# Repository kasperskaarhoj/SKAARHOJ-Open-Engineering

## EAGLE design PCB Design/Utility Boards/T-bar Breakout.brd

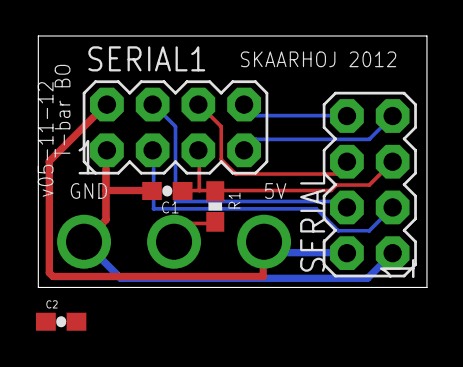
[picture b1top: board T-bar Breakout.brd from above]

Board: 2 copper layers, 21.6 x 14.0 mm, 5 parts (0 on the bottom side), 8 nets.

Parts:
C1: 1uF; 0603-CAP
C2: 10uF; 0603-CAP
R1: 10K; 0603-RES
SERIAL, SERIAL1: M04X2; 2X4

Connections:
5V: C2.1, SERIAL.2, SERIAL1.2
DISP_DATA_OUT: SERIAL.6, SERIAL1.6
GND: C1.2, C2.2, SERIAL.1, SERIAL1.1
I2C_SCL: SERIAL.4, SERIAL1.4
I2C_SDA: SERIAL.3, SERIAL1.3
SDI_MOSI: SERIAL.8, SERIAL1.8
SDI_SCLK: SERIAL.7, SERIAL1.7
SLIDER_IN: C1.1, R1.1, SERIAL.5, SERIAL1.5

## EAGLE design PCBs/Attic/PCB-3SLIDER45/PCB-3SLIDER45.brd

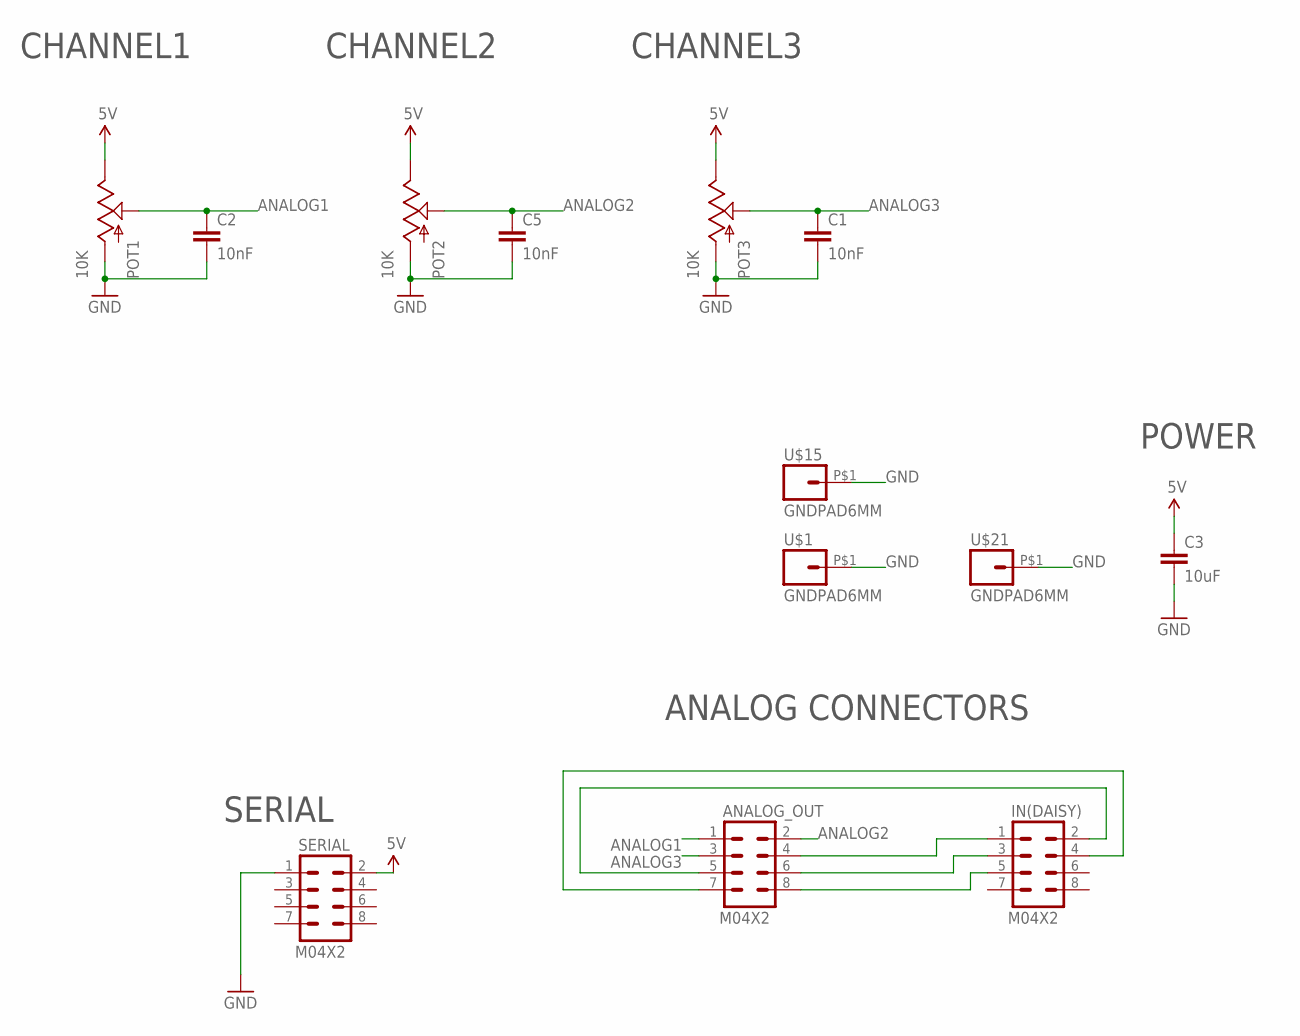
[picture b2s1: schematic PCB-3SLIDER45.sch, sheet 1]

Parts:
ANALOG_OUT: M04X2; 2X4
C1, C2, C5: 10nF; 0603-CAP
C3: 10uF; 0805
IN(DAISY): M04X2; 2X4
POT1, POT2, POT3: 10K; SLIDER45
SERIAL: M04X2; 2X4
U$1, U$15, U$21: GNDPAD6MM; 3.2MMPAD6MM

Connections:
5V: C3.1, POT1.1 (E), POT2.1 (E), POT3.1 (E), SERIAL.2
ANALOG1: ANALOG_OUT.1, C2.1, POT1.2A (S)
ANALOG2: ANALOG_OUT.2, C5.1, POT2.2A (S)
ANALOG3: ANALOG_OUT.3, C1.1, POT3.2A (S)
GND: C1.2, C2.2, C3.2, C5.2, POT1.3 (A), POT2.3 (A), POT3.3 (A), SERIAL.1, U$1.P$1, U$15.P$1, U$21.P$1
unnamed: ANALOG_OUT.4, IN(DAISY).1
unnamed: ANALOG_OUT.5, IN(DAISY).2
unnamed: ANALOG_OUT.6, IN(DAISY).3
unnamed: ANALOG_OUT.7, IN(DAISY).4
unnamed: ANALOG_OUT.8, IN(DAISY).5

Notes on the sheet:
SERIAL
POWER
ANALOG CONNECTORS
CHANNEL3
CHANNEL1
CHANNEL2

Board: 2 copper layers, 13 parts (7 on the bottom side), 10 nets, no tracks yet.

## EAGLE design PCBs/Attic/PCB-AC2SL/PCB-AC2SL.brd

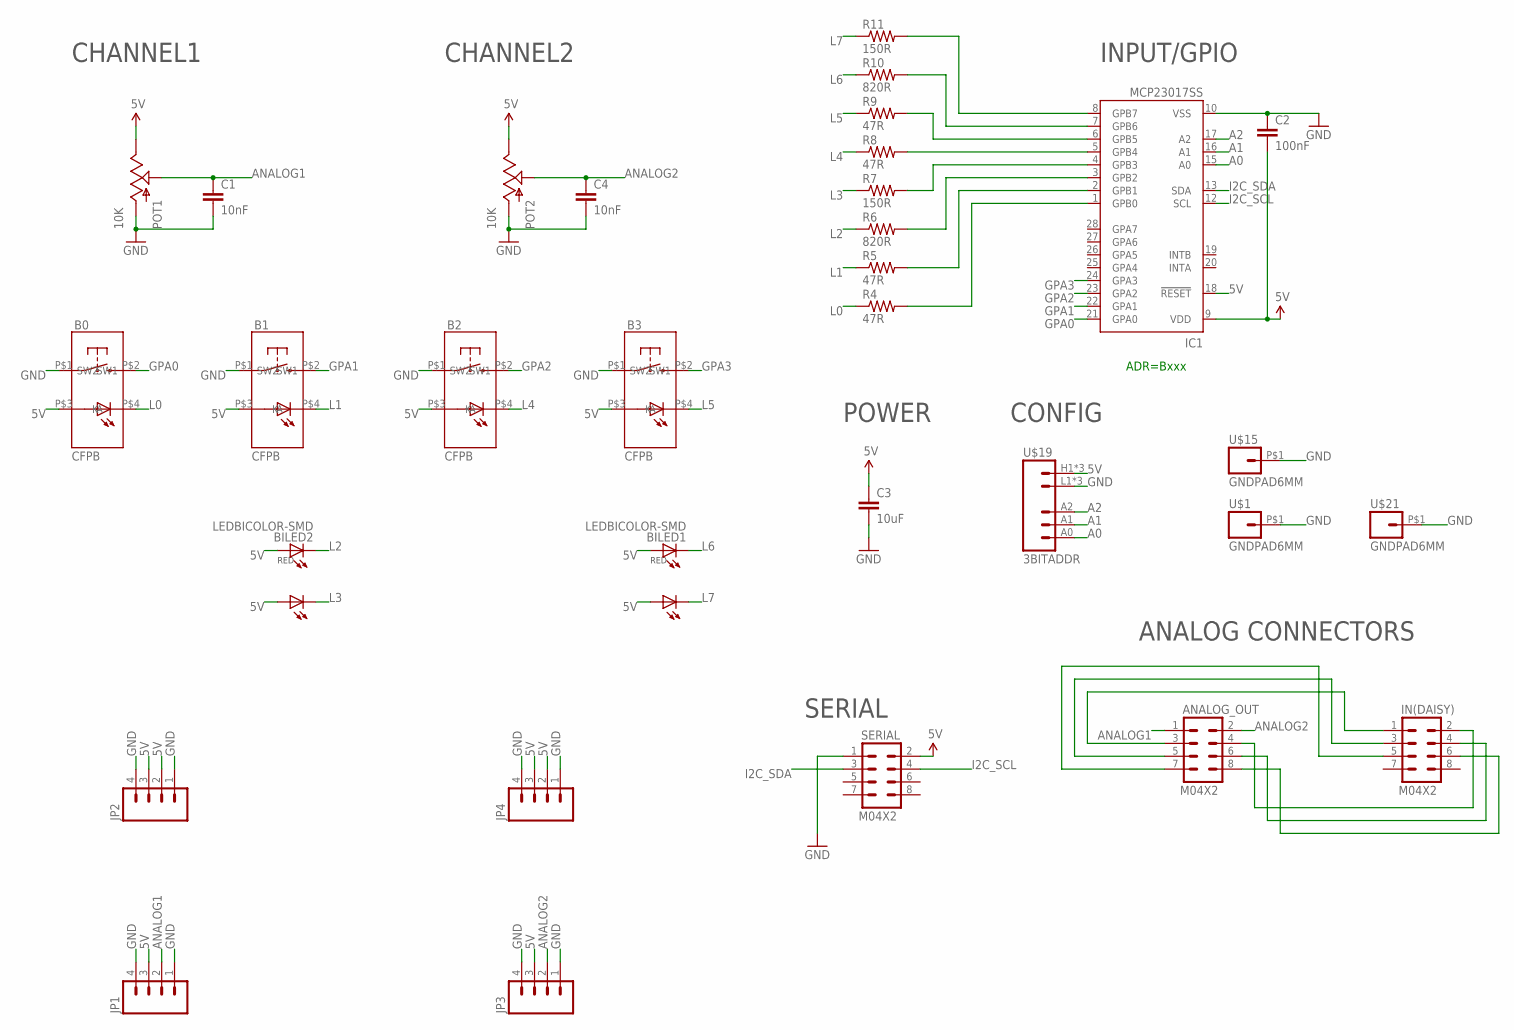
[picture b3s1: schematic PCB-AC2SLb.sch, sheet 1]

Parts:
ANALOG_OUT: M04X2; 2X4
B0, B1, B2, B3: CFPB; CFPB-6/9MM
BILED1, BILED2: LEDBICOLOR-SMD
C1, C4: 10nF; 0603-CAP
C2: 100nF; 0603-CAP
C3: 10uF; 0805
IC1: MCP23017SS; SSOP28; MPN MCP23017-E/SS
IN(DAISY): M04X2; 2X4
JP1, JP2, JP3, JP4: M04PTH; 1X04
POT1, POT2: 10K; SLIDER45
R4, R5, R8, R9: 47R; 0603-RES
R6, R10: 820R; 0603-RES
R7, R11: 150R; 0603-RES
SERIAL: M04X2; 2X4
U$1, U$15, U$21: GNDPAD6MM; 3.2MMPAD6MM
U$19: 3BITADDR

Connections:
5V: B0.P$3 (A), B1.P$3 (A), B2.P$3 (A), B3.P$3 (A), BILED1.P$1 (A), BILED1.P$3 (A1), BILED2.P$1 (A), BILED2.P$3 (A1), C2.2, C3.1, IC1.9 (VDD), IC1.18 (!RESET), JP1.3, JP2.2, JP2.3, JP3.3, JP4.2, JP4.3, POT1.1 (E), POT2.1 (E), SERIAL.2, U$19.H1 (VCC), U$19.H2 (VCC), U$19.H3 (VCC)
A0: IC1.15 (A0), U$19.A0
A1: IC1.16 (A1), U$19.A1
A2: IC1.17 (A2), U$19.A2
ANALOG1: ANALOG_OUT.1, C1.1, JP1.2, POT1.2A (S)
ANALOG2: ANALOG_OUT.2, C4.1, JP3.2, POT2.2A (S)
GND: B0.P$1 (SW1), B1.P$1 (SW1), B2.P$1 (SW1), B3.P$1 (SW1), C1.2, C2.1, C3.2, C4.2, IC1.10 (VSS), JP1.1, JP1.4, JP2.1, JP2.4, JP3.1, JP3.4, JP4.1, JP4.4, POT1.3 (A), POT2.3 (A), SERIAL.1, U$1.P$1, U$15.P$1, U$19.L1 (GND), U$19.L2 (GND), U$19.L3 (GND), U$21.P$1
GPA0: B0.P$2 (SW2), IC1.21 (GPA0)
GPA1: B1.P$2 (SW2), IC1.22 (GPA1)
GPA2: B2.P$2 (SW2), IC1.23 (GPA2)
GPA3: B3.P$2 (SW2), IC1.24 (GPA3)
I2C_SCL: IC1.12 (SCL), SERIAL.4
I2C_SDA: IC1.13 (SDA), SERIAL.3
L0: B0.P$4 (K), R4.1
L1: B1.P$4 (K), R5.1
L2: BILED2.P$2 (C), R6.1
L3: BILED2.P$4 (C1), R7.1
L4: B2.P$4 (K), R8.1
L5: B3.P$4 (K), R9.1
L6: BILED1.P$2 (C), R10.1
L7: BILED1.P$4 (C1), R11.1
unnamed: IC1.4 (GPB3), R7.2
unnamed: IC1.5 (GPB4), R8.2
unnamed: IC1.6 (GPB5), R9.2
unnamed: IC1.7 (GPB6), R10.2
unnamed: IC1.8 (GPB7), R11.2
unnamed: IC1.3 (GPB2), R6.2
unnamed: IC1.2 (GPB1), R5.2
unnamed: IC1.1 (GPB0), R4.2
unnamed: ANALOG_OUT.3, IN(DAISY).1
unnamed: ANALOG_OUT.5, IN(DAISY).3
unnamed: ANALOG_OUT.7, IN(DAISY).5
unnamed: ANALOG_OUT.4, IN(DAISY).2
unnamed: ANALOG_OUT.6, IN(DAISY).4
unnamed: ANALOG_OUT.8, IN(DAISY).6

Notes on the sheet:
SERIAL
ADR=Bxxx
INPUT/GPIO
POWER
ANALOG CONNECTORS
CHANNEL1
CHANNEL2
CONFIG

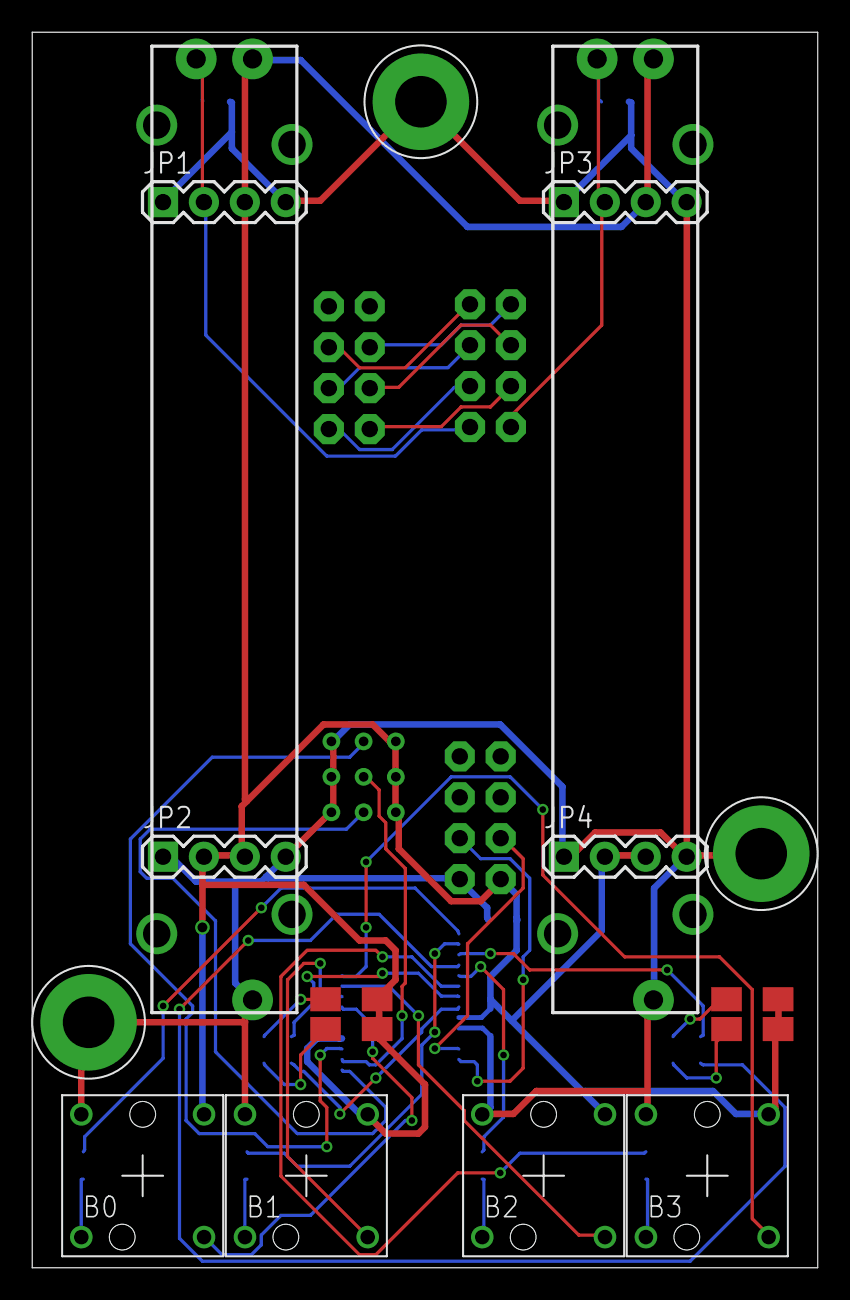
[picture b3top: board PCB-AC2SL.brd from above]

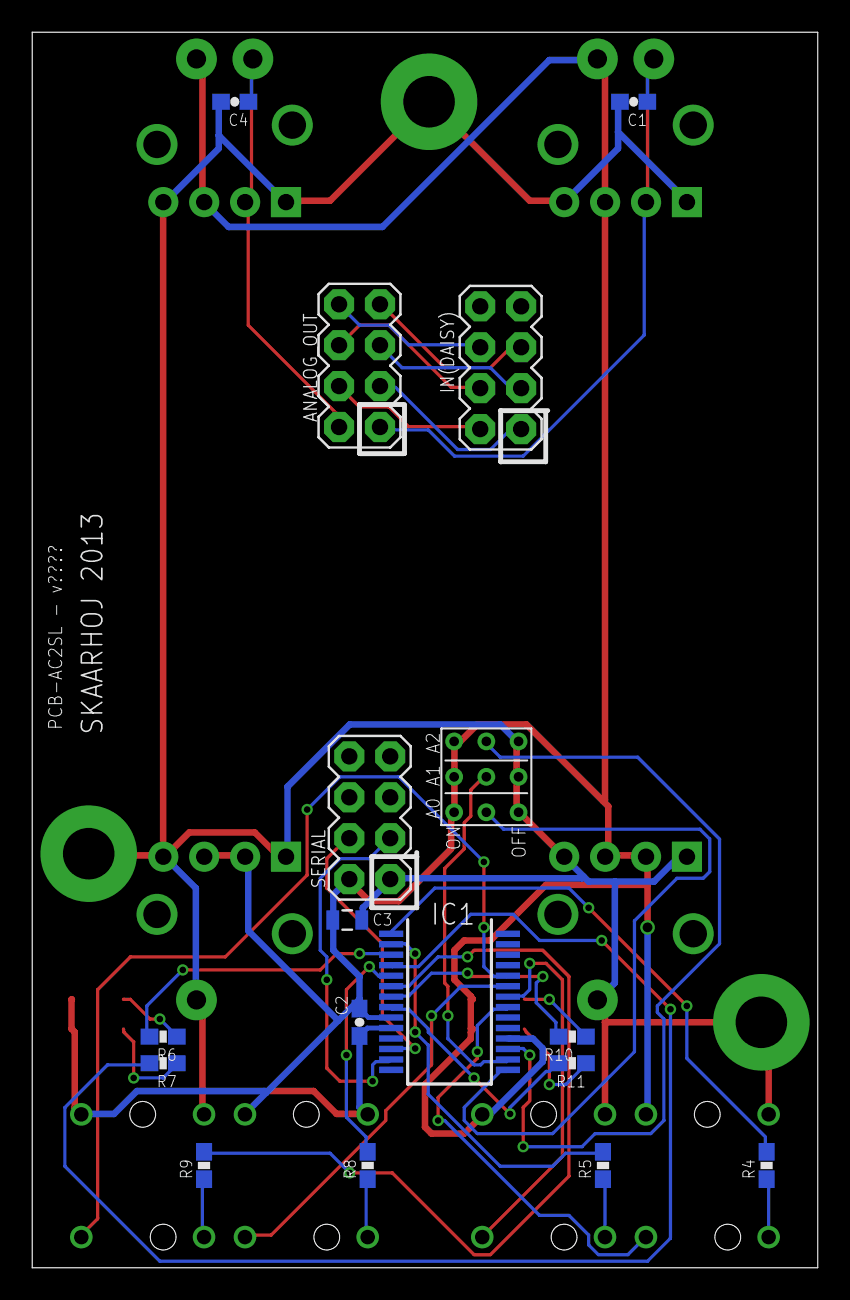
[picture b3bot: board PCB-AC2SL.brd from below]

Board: 2 copper layers, 48.8 x 76.7 mm, 32 parts (17 on the bottom side), 35 nets.

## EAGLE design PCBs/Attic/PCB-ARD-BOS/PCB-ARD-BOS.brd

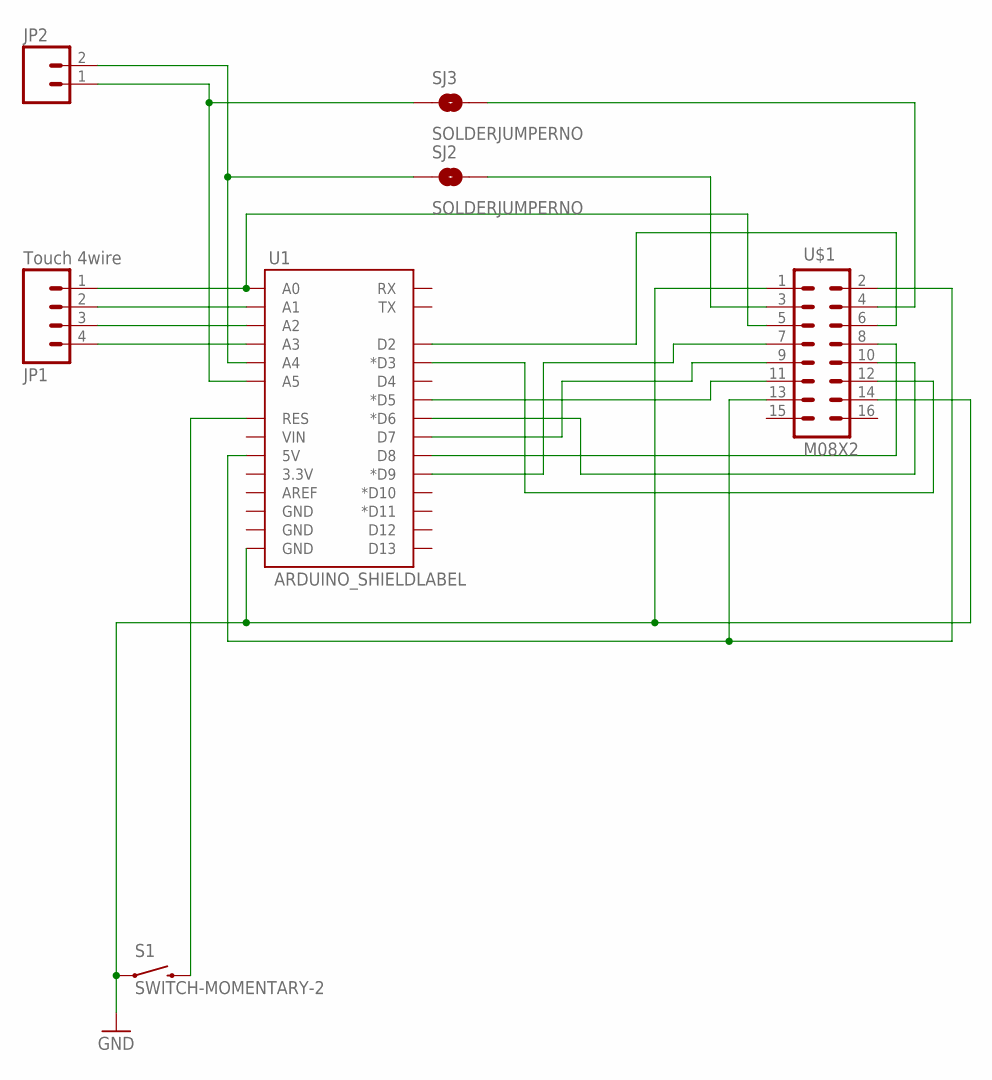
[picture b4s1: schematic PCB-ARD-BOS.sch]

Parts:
JP1: Touch 4wire; 1X04
JP2: M02PTH; 1X02
S1: SWITCH-MOMENTARY-2; TACTILE_SWITCH_TALL
SJ2, SJ3: SOLDERJUMPERNO; SJ_2S-NO
U1: ARDUINO_SHIELDLABEL; DUEMILANOVE_SHIELD
U$1: M08X2; 2X8

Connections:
GND: S1.A2 (1), U1.GND@0 (GND), U$1.1, U$1.14
unnamed: U1.D9 (*D9), U$1.7
unnamed: U1.5V, U$1.2, U$1.13
unnamed: JP2.2, SJ2.1, U1.A4
unnamed: JP2.1, SJ3.1, U1.A5
unnamed: JP1.1, U1.A0, U$1.5
unnamed: U1.D2, U$1.6
unnamed: U1.D5 (*D5), U$1.11
unnamed: U1.D8, U$1.8
unnamed: U1.D7, U$1.9
unnamed: U1.D6 (*D6), U$1.10
unnamed: JP1.2, U1.A1
unnamed: U1.D3 (*D3), U$1.12
unnamed: SJ3.2, U$1.4
unnamed: JP1.3, U1.A2
unnamed: JP1.4, U1.A3
unnamed: SJ2.2, U$1.3
unnamed: S1.B2 (2), U1.RES

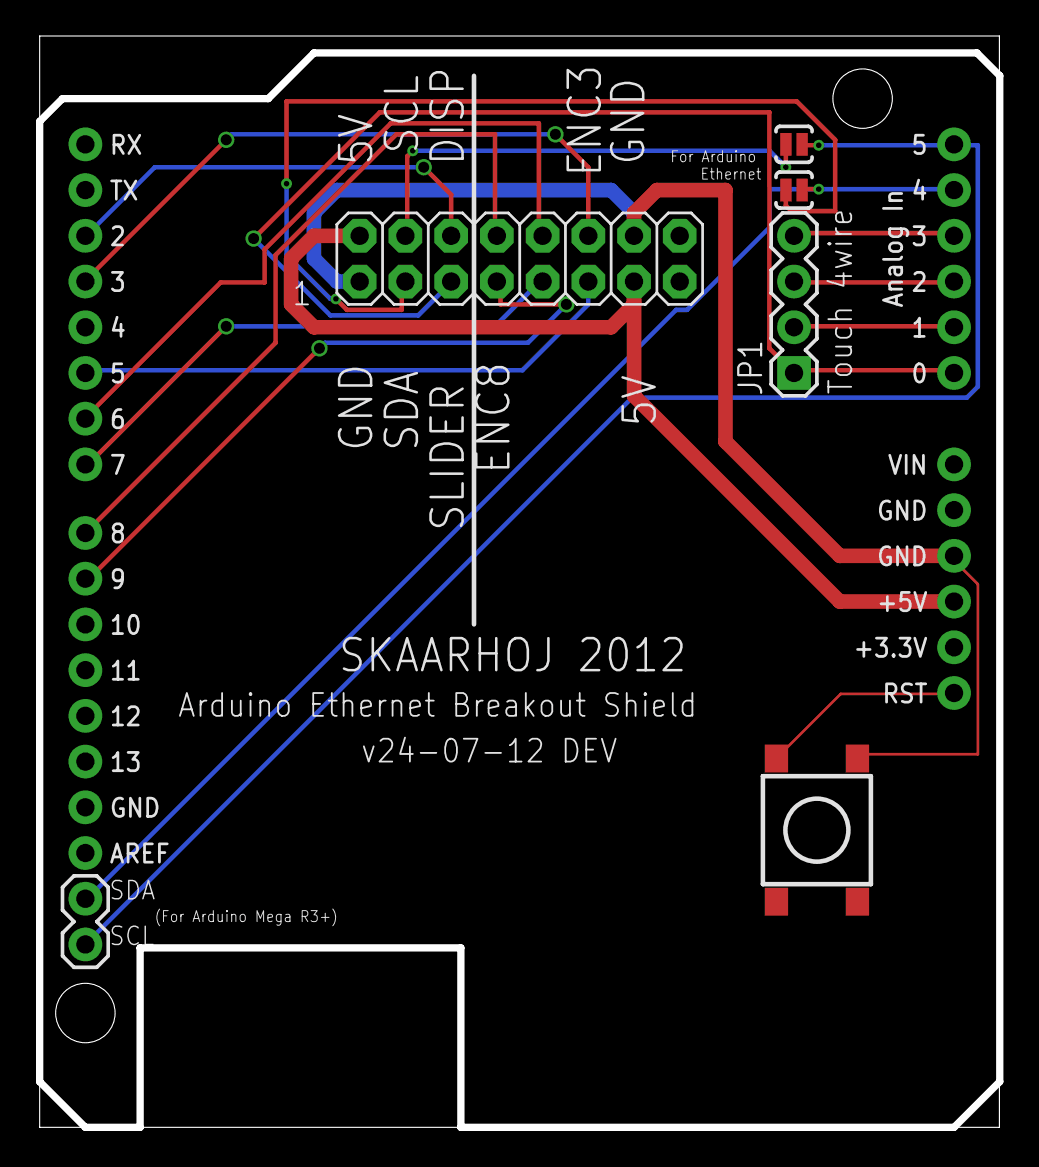
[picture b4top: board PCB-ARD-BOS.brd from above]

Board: 2 copper layers, 53.3 x 60.6 mm, 7 parts (0 on the bottom side), 18 nets.

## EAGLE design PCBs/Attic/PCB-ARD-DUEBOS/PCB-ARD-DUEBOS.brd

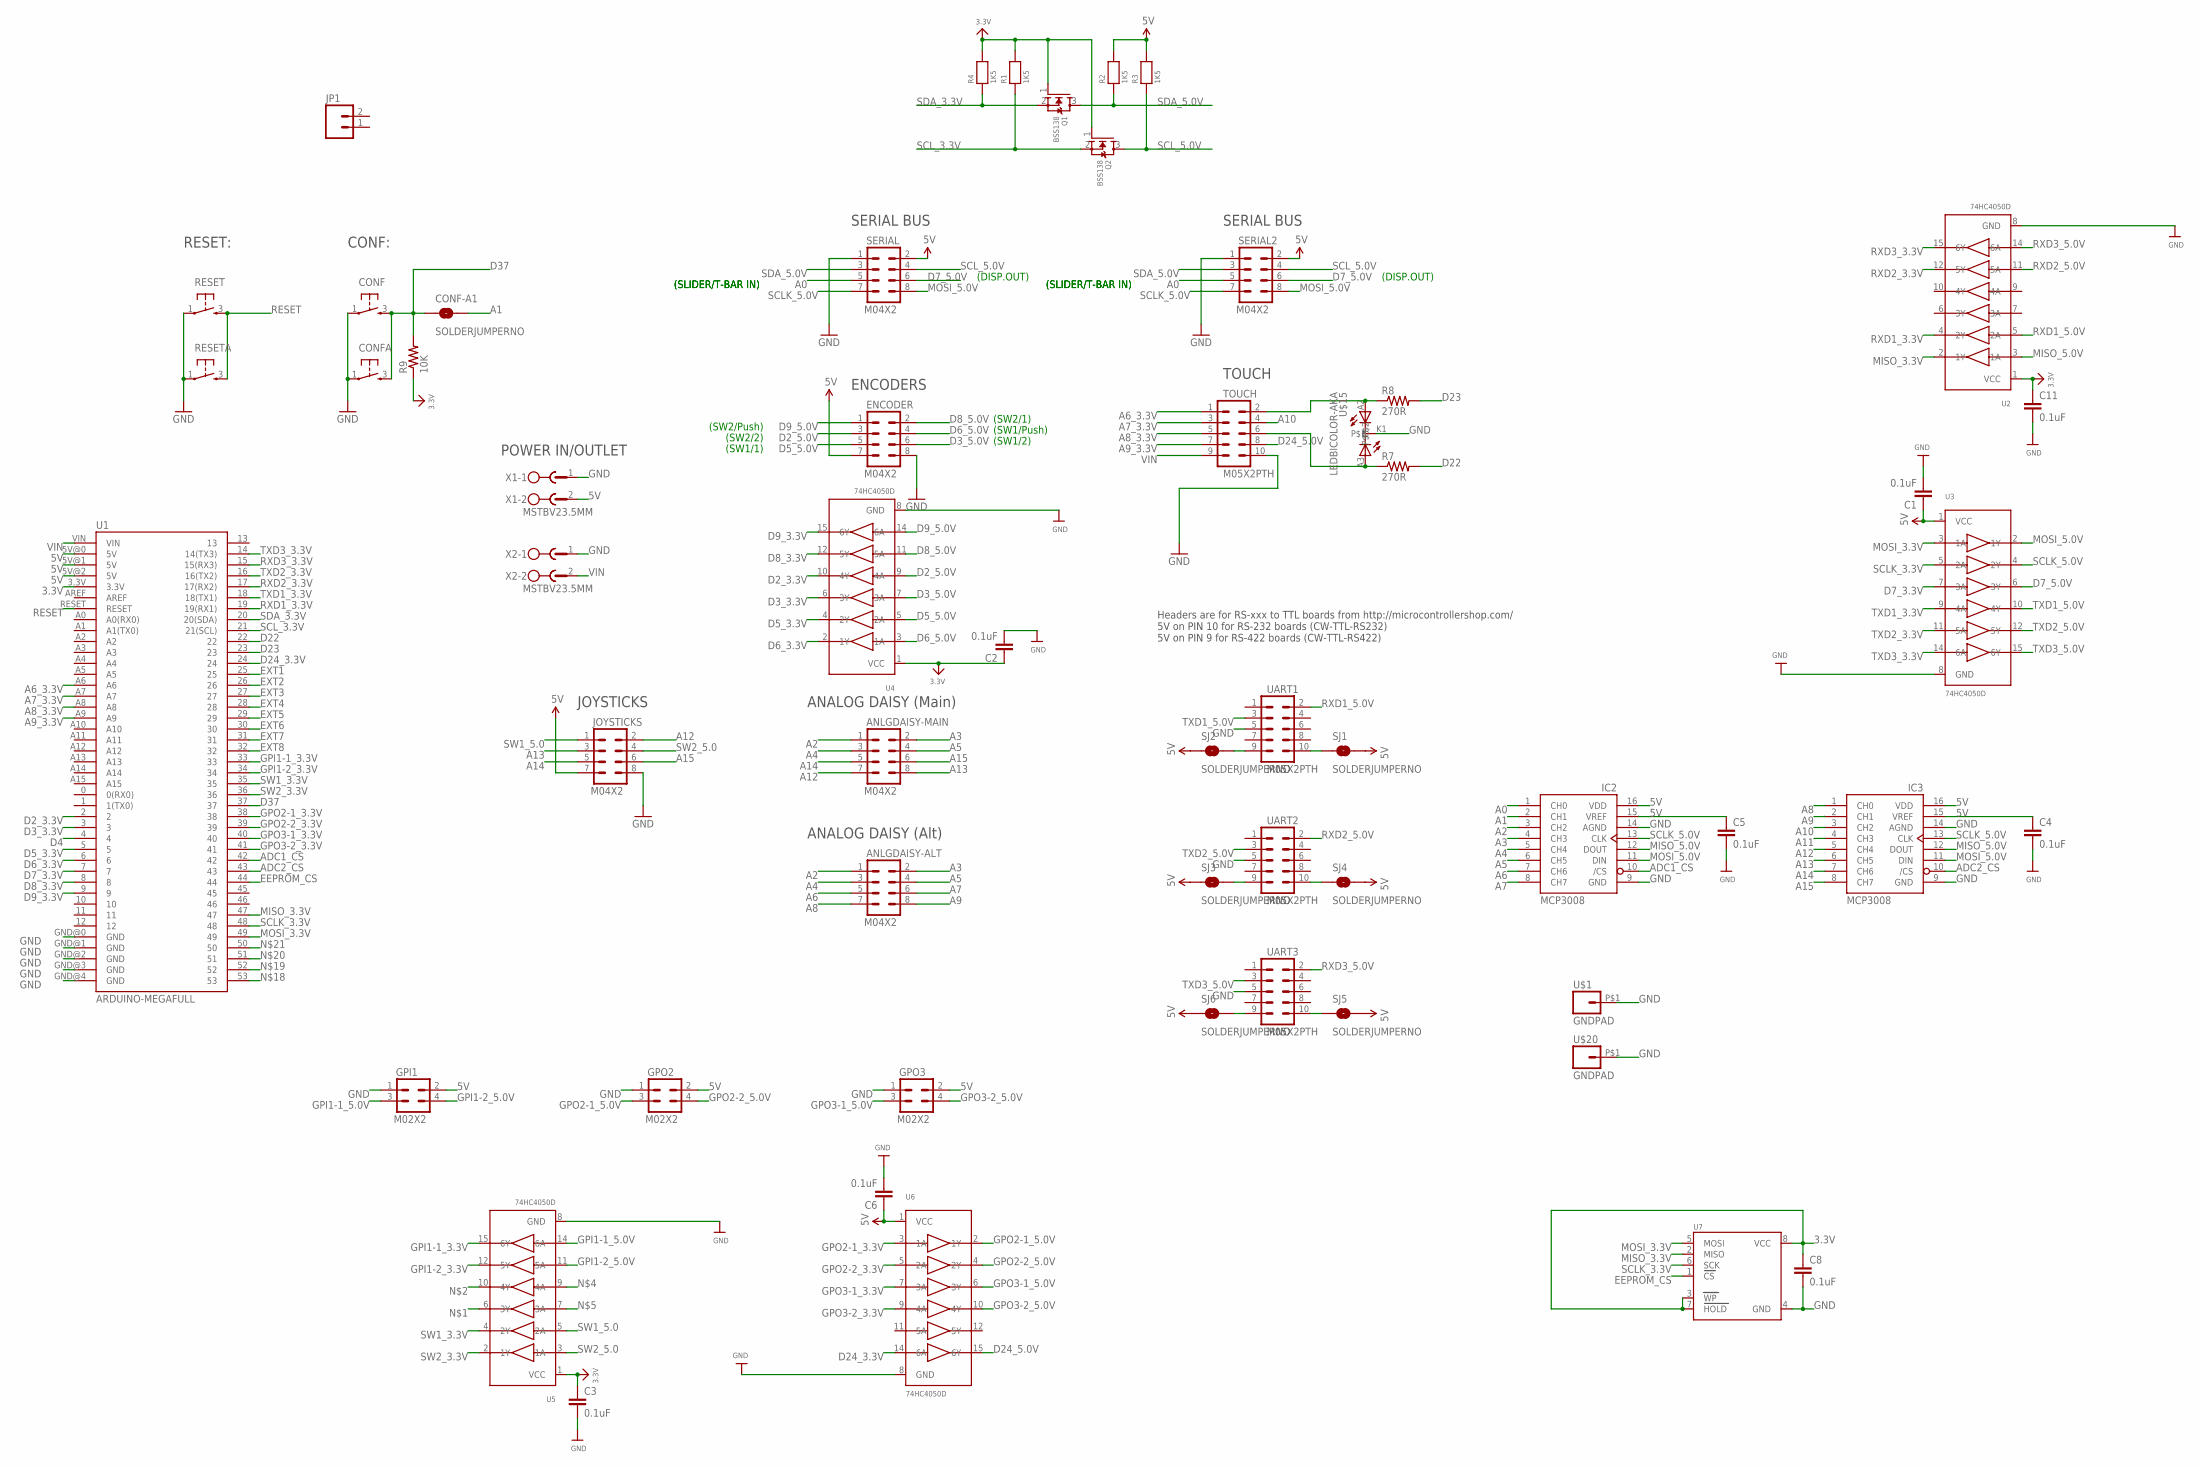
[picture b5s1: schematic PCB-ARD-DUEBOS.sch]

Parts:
ANLGDAISY-ALT: M04X2; 2X4
ANLGDAISY-MAIN: M04X2; 2X4
C1, C2, C3, C4, C5, C6, C8, C11: 0.1uF; 0603-CAP
CONF: TAC_SWITCH; PUSHBUTTON
CONF-A1: SOLDERJUMPERNO; SJ_2S-NO
CONFA: TAC_SWITCH; PUSHBUTTON
ENCODER: M04X2; 2X4
GPI1: M02X2; 2X2
GPO2, GPO3: M02X2; 2X2
IC2, IC3: MCP3008SOIC; SOIC16
JOYSTICKS: M04X2; 2X4
JP1: M02PTH; 1X02
Q1, Q2: BSS138; SOT23-R
R1, R2, R3, R4: 1K5; 0603
R7, R8: 270R; 0603-RES
R9: 10K; 0603-RES
RESET: TAC_SWITCH; PUSHBUTTON
RESETA: TAC_SWITCH; PUSHBUTTON
SERIAL, SERIAL2: M04X2; 2X4
SJ1, SJ2, SJ3, SJ4, SJ5, SJ6: SOLDERJUMPERNO; SJ_2S-NO
TOUCH: M05X2PTH; AVR_ICSP
U1: ARDUINO-MEGAFULL; ARDUINO_MEGA
U2, U3, U4, U5, U6: 74HC4050D; TSSOP16
U7: EEPROM_SPI_AT25040ATSSOP; TSSOP8-4.4MM
U$1, U$20: GNDPAD; 3.2MMPAD
U$15: LEDBICOLOR-AKA; LED5MM-BICOLOR
UART1, UART2, UART3: M05X2PTH; AVR_ICSP
X1, X2: MSTBV23.5MM; MSTBV2-3.5

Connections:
3.3V: C2.1, C3.1, C8.1, C11.1, Q1.1 (G), Q2.1 (G), R1.2, R4.2, R9.1, U1.3.3V, U2.1 (VCC), U4.1 (VCC), U5.1 (VCC), U7.3 (WP), U7.7 (HOLD), U7.8 (VCC)
5V: C1.1, C4.1, C5.1, C6.1, ENCODER.7, GPI1.2, GPO2.2, GPO3.2, IC2.15 (VREF), IC2.16 (VDD), IC3.15 (VREF), IC3.16 (VDD), JOYSTICKS.7, R2.2, R3.2, SERIAL.2, SERIAL2.2, SJ1.2, SJ2.1, SJ3.1, SJ4.2, SJ5.2, SJ6.1, U1.5V@0 (5V), U1.5V@1 (5V), U1.5V@2 (5V), U3.1 (VCC), U6.1 (VCC), X1.2
A0: IC2.1 (CH0), SERIAL.5, SERIAL2.5
A1: CONF-A1.2, IC2.2 (CH1)
A2: ANLGDAISY-ALT.1, ANLGDAISY-MAIN.1, IC2.3 (CH2)
A3: ANLGDAISY-ALT.2, ANLGDAISY-MAIN.2, IC2.4 (CH3)
A4: ANLGDAISY-ALT.3, ANLGDAISY-MAIN.3, IC2.5 (CH4)
A5: ANLGDAISY-ALT.4, ANLGDAISY-MAIN.4, IC2.6 (CH5)
A6: ANLGDAISY-ALT.5, IC2.7 (CH6)
A6_3.3V: TOUCH.1, U1.A6
A7: ANLGDAISY-ALT.6, IC2.8 (CH7)
A7_3.3V: TOUCH.3, U1.A7
A8: ANLGDAISY-ALT.7, IC3.1 (CH0)
A8_3.3V: TOUCH.5, U1.A8
A9: ANLGDAISY-ALT.8, IC3.2 (CH1)
A9_3.3V: TOUCH.7, U1.A9
A10: IC3.3 (CH2), TOUCH.4
A11: IC3.4 (CH3)
A12: ANLGDAISY-MAIN.7, IC3.5 (CH4), JOYSTICKS.2
A13: ANLGDAISY-MAIN.8, IC3.6 (CH5), JOYSTICKS.3
A14: ANLGDAISY-MAIN.5, IC3.7 (CH6), JOYSTICKS.5
A15: ANLGDAISY-MAIN.6, IC3.8 (CH7), JOYSTICKS.6
ADC1_CS: IC2.10 (/CS), U1.42
ADC2_CS: IC3.10 (/CS), U1.43
D2_3.3V: U1.2, U4.10 (4Y)
D2_5.0V: ENCODER.3, U4.9 (4A)
D3_3.3V: U1.3, U4.6 (3Y)
D3_5.0V: ENCODER.6, U4.7 (3A)
D4: U1.4
D5_3.3V: U1.5, U4.4 (2Y)
D5_5.0V: ENCODER.5, U4.5 (2A)
D6_3.3V: U1.6, U4.2 (1Y)
D6_5.0V: ENCODER.4, U4.3 (1A)
D7_3.3V: U1.7, U3.7 (3A)
D7_5.0V: SERIAL.6, SERIAL2.6, U3.6 (3Y)
D8_3.3V: U1.8, U4.12 (5Y)
D8_5.0V: ENCODER.2, U4.11 (5A)
D9_3.3V: U1.9, U4.15 (6Y)
D9_5.0V: ENCODER.1, U4.14 (6A)
D22: R7.2, U1.22
D23: R8.2, U1.23
D24_3.3V: U1.24, U6.14 (6A)
D24_5.0V: TOUCH.8, U6.15 (6Y)
D37: CONF.3, CONF-A1.1, CONFA.3, R9.2, U1.37
EEPROM_CS: U1.44, U7.1 (CS)
EXT1: U1.25
EXT2: U1.26
EXT3: U1.27
EXT4: U1.28
EXT5: U1.29
EXT6: U1.30
EXT7: U1.31
EXT8: U1.32
GND: C1.2, C2.2, C3.2, C4.2, C5.2, C6.2, C8.2, C11.2, CONF.1, CONFA.1, ENCODER.8, GPI1.1, GPO2.1, GPO3.1, IC2.9 (GND), IC2.14 (AGND), IC3.9 (GND), IC3.14 (AGND), JOYSTICKS.8, RESET.1, RESETA.1, SERIAL.1, SERIAL2.1, TOUCH.10, U1.GND@0 (GND), U1.GND@1 (GND), U1.GND@2 (GND), U1.GND@3 (GND), U1.GND@4 (GND), U2.8 (GND), U3.8 (GND), U4.8 (GND), U5.8 (GND), U6.8 (GND), U7.4 (GND), U$1.P$1, U$15.K1, U$20.P$1, UART1.5, UART2.5, UART3.5, X1.1, X2.1
GPI1-1_3.3V: U1.33, U5.15 (6Y)
GPI1-1_5.0V: GPI1.3, U5.14 (6A)
GPI1-2_3.3V: U1.34, U5.12 (5Y)
GPI1-2_5.0V: GPI1.4, U5.11 (5A)
GPO2-1_3.3V: U1.38, U6.3 (1A)
GPO2-1_5.0V: GPO2.3, U6.2 (1Y)
GPO2-2_3.3V: U1.39, U6.5 (2A)
GPO2-2_5.0V: GPO2.4, U6.4 (2Y)
GPO3-1_3.3V: U1.40, U6.7 (3A)
GPO3-1_5.0V: GPO3.3, U6.6 (3Y)
GPO3-2_3.3V: U1.41, U6.9 (4A)
GPO3-2_5.0V: GPO3.4, U6.10 (4Y)
MISO_3.3V: U1.47, U2.2 (1Y), U7.2 (MISO)
MISO_5.0V: IC2.12 (DOUT), IC3.12 (DOUT), U2.3 (1A)
MOSI_3.3V: U1.49, U3.3 (1A), U7.5 (MOSI)
MOSI_5.0V: IC2.11 (DIN), IC3.11 (DIN), SERIAL.8, SERIAL2.8, U3.2 (1Y)
unnamed: SJ6.2, UART3.9
unnamed: SJ3.2, UART2.9
unnamed: SJ2.2, UART1.9
unnamed: SJ1.1, UART1.10
unnamed: SJ4.1, UART2.10
unnamed: SJ5.1, UART3.10
unnamed: R8.1, TOUCH.2, U$15.A2
unnamed: R7.1, TOUCH.6, U$15.A3
RESET: RESET.3, RESETA.3, U1.RESET
RXD1_3.3V: U1.19 (19(RX1)), U2.4 (2Y)
RXD1_5.0V: U2.5 (2A), UART1.2
RXD2_3.3V: U1.17 (17(RX2)), U2.12 (5Y)
RXD2_5.0V: U2.11 (5A), UART2.2
RXD3_3.3V: U1.15 (15(RX3)), U2.15 (6Y)
RXD3_5.0V: U2.14 (6A), UART3.2
SCLK_3.3V: U1.48, U3.5 (2A), U7.6 (SCK)
SCLK_5.0V: IC2.13 (CLK), IC3.13 (CLK), SERIAL.7, SERIAL2.7, U3.4 (2Y)
SCL_3.3V: Q2.2 (S), R1.1, U1.21 (21(SCL))
SCL_5.0V: Q2.3 (D), R3.1, SERIAL.4, SERIAL2.4
SDA_3.3V: Q1.2 (S), R4.1, U1.20 (20(SDA))
SDA_5.0V: Q1.3 (D), R2.1, SERIAL.3, SERIAL2.3
SW1_3.3V: U1.35, U5.4 (2Y)
SW1_5.0: JOYSTICKS.1, U5.5 (2A)
SW2_3.3V: U1.36, U5.2 (1Y)
SW2_5.0: JOYSTICKS.4, U5.3 (1A)
TXD1_3.3V: U1.18 (18(TX1)), U3.9 (4A)
TXD1_5.0V: U3.10 (4Y), UART1.3
TXD2_3.3V: U1.16 (16(TX2)), U3.11 (5A)
TXD2_5.0V: U3.12 (5Y), UART2.3
TXD3_3.3V: U1.14 (14(TX3)), U3.14 (6A)
TXD3_5.0V: U3.15 (6Y), UART3.3
VIN: TOUCH.9, U1.VIN, X2.2

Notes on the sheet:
JOYSTICKS
Headers are for RS-xxx to TTL boards from http://microcontrollershop.com/ 5V on PIN 10 for RS-232 boards (CW-TTL-RS232) 5V on PIN 9 for RS-422 boards (CW-TTL-RS422)
ENCODERS
SERIAL BUS
TOUCH
(SLIDER/T-BAR IN)
(SW2/Push)
(SW2/2)
(SW1/1)
(SW2/1)
(SW1/Push)
(SW1/2)
(DISP.OUT)
RESET:
CONF:
ANALOG DAISY (Main)
ANALOG DAISY (Alt)
POWER IN/OUTLET

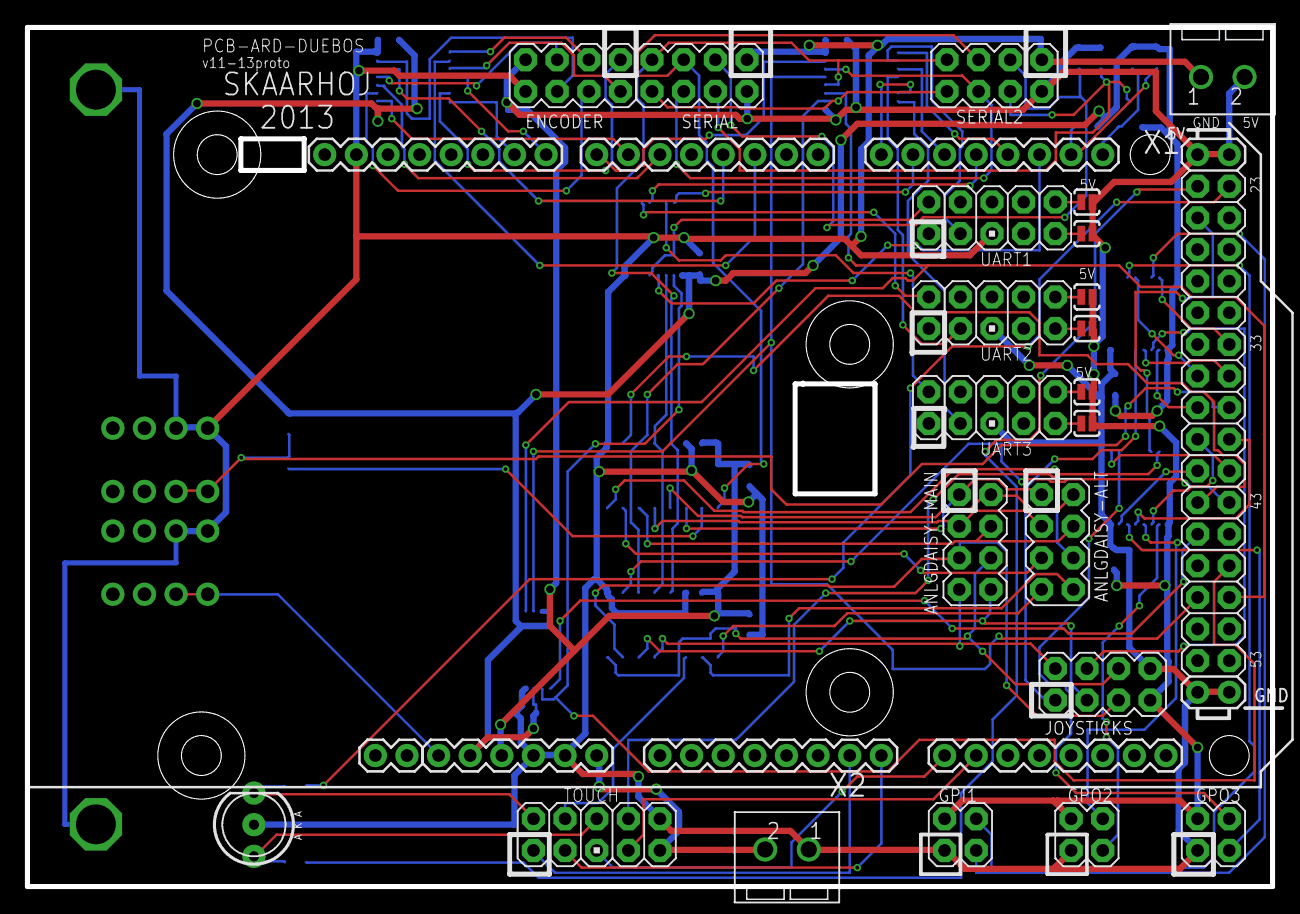
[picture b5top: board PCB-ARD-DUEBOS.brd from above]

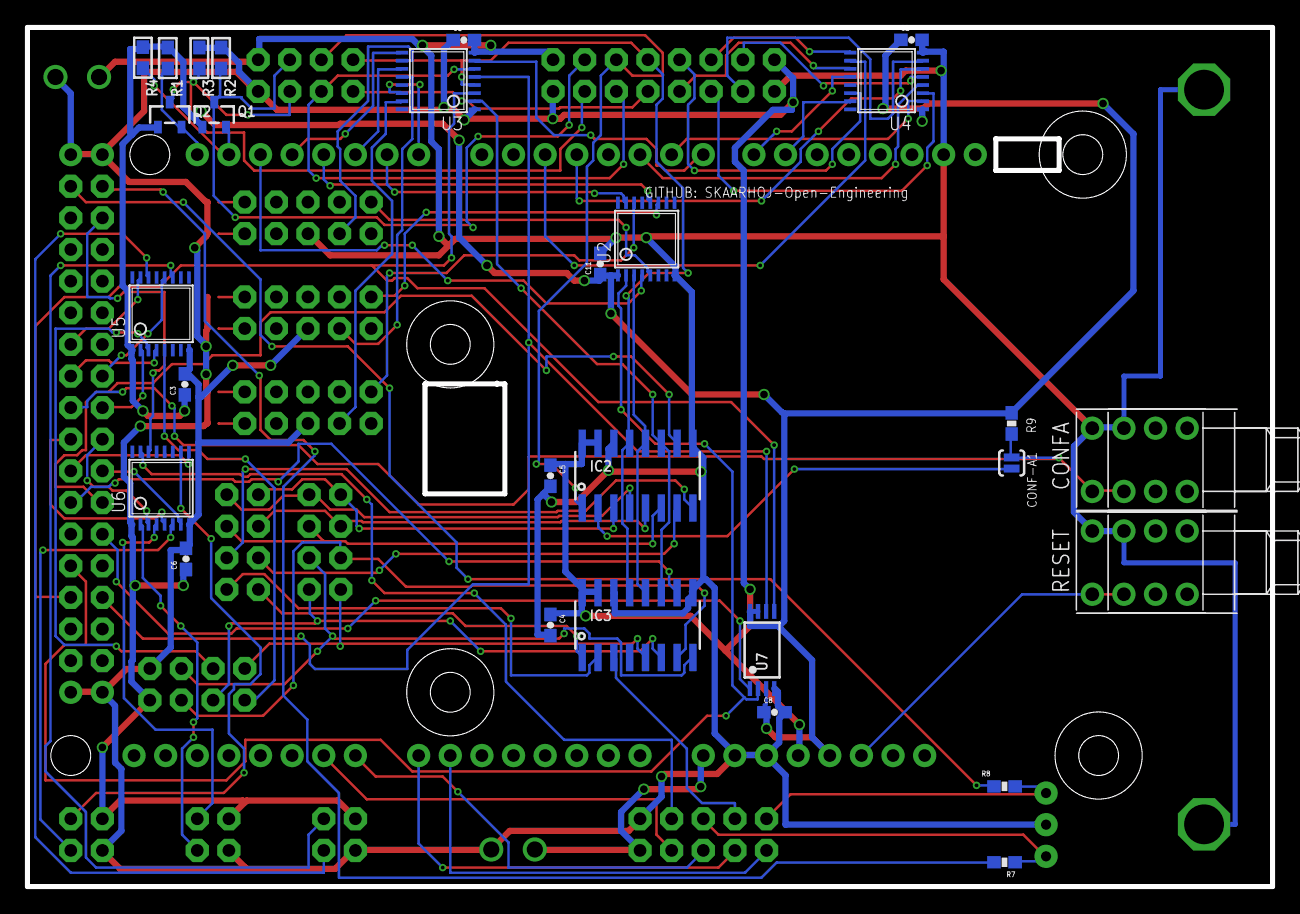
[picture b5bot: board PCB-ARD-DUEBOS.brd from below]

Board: 2 copper layers, 100.0 x 69.0 mm, 56 parts (30 on the bottom side), 92 nets.

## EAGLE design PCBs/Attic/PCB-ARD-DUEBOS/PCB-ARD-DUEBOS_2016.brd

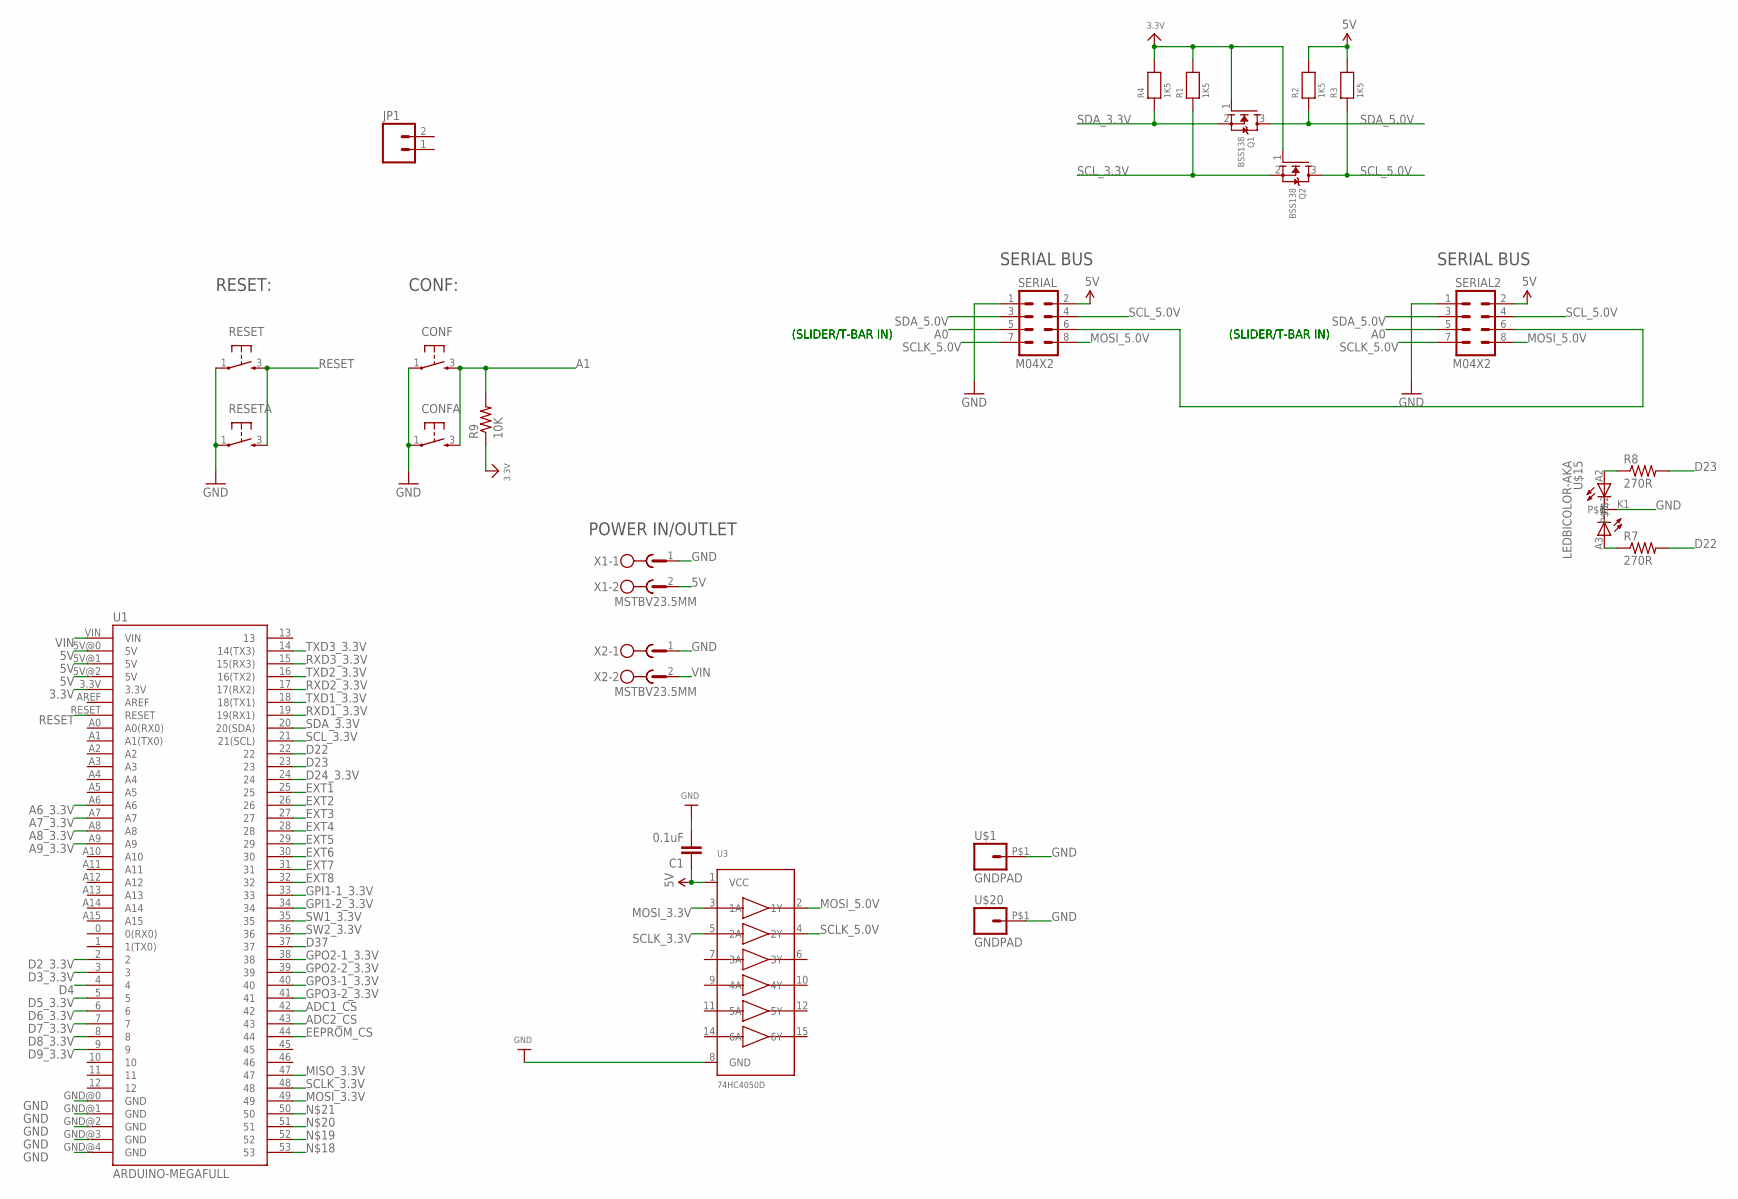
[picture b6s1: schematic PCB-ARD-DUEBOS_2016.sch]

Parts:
C1: 0.1uF; 0603-CAP
CONF: TAC_SWITCH; PUSHBUTTON
CONFA: TAC_SWITCH; PUSHBUTTON
JP1: M02PTH; 1X02
Q1, Q2: BSS138; SOT23-R
R1, R2, R3, R4: 1K5; 0603
R7, R8: 270R; 0603-RES
R9: 10K; 0603-RES
RESET: TAC_SWITCH; PUSHBUTTON
RESETA: TAC_SWITCH; PUSHBUTTON
SERIAL, SERIAL2: M04X2; 2X4
U1: ARDUINO-MEGAFULL; ARDUINO_MEGA
U3: 74HC4050D; TSSOP16
U$1, U$20: GNDPAD; 3.2MMPAD
U$15: LEDBICOLOR-AKA; LED5MM-BICOLOR
X1, X2: MSTBV23.5MM; MSTBV2-3.5

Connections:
3.3V: Q1.1 (G), Q2.1 (G), R1.2, R4.2, R9.1, U1.3.3V
5V: C1.1, R2.2, R3.2, SERIAL.2, SERIAL2.2, U1.5V@0 (5V), U1.5V@1 (5V), U1.5V@2 (5V), U3.1 (VCC), X1.2
A0: SERIAL.5, SERIAL2.5
A1: CONF.3, CONFA.3, R9.2
A6_3.3V: U1.A6
A7_3.3V: U1.A7
A8_3.3V: U1.A8
A9_3.3V: U1.A9
ADC1_CS: U1.42
ADC2_CS: U1.43
D2_3.3V: U1.2
D3_3.3V: U1.3
D4: U1.4
D5_3.3V: U1.5
D6_3.3V: U1.6
D7_3.3V: U1.7
D8_3.3V: U1.8
D9_3.3V: U1.9
D22: R7.2, U1.22
D23: R8.2, U1.23
D24_3.3V: U1.24
D37: U1.37
EEPROM_CS: U1.44
EXT1: U1.25
EXT2: U1.26
EXT3: U1.27
EXT4: U1.28
EXT5: U1.29
EXT6: U1.30
EXT7: U1.31
EXT8: U1.32
GND: C1.2, CONF.1, CONFA.1, RESET.1, RESETA.1, SERIAL.1, SERIAL2.1, U1.GND@0 (GND), U1.GND@1 (GND), U1.GND@2 (GND), U1.GND@3 (GND), U1.GND@4 (GND), U3.8 (GND), U$1.P$1, U$15.K1, U$20.P$1, X1.1, X2.1
GPI1-1_3.3V: U1.33
GPI1-2_3.3V: U1.34
GPO2-1_3.3V: U1.38
GPO2-2_3.3V: U1.39
GPO3-1_3.3V: U1.40
GPO3-2_3.3V: U1.41
MISO_3.3V: U1.47
MOSI_3.3V: U1.49, U3.3 (1A)
MOSI_5.0V: SERIAL.8, SERIAL2.8, U3.2 (1Y)
unnamed: SERIAL.6, SERIAL2.6
unnamed: R8.1, U$15.A2
unnamed: R7.1, U$15.A3
RESET: RESET.3, RESETA.3, U1.RESET
RXD1_3.3V: U1.19 (19(RX1))
RXD2_3.3V: U1.17 (17(RX2))
RXD3_3.3V: U1.15 (15(RX3))
SCLK_3.3V: U1.48, U3.5 (2A)
SCLK_5.0V: SERIAL.7, SERIAL2.7, U3.4 (2Y)
SCL_3.3V: Q2.2 (S), R1.1, U1.21 (21(SCL))
SCL_5.0V: Q2.3 (D), R3.1, SERIAL.4, SERIAL2.4
SDA_3.3V: Q1.2 (S), R4.1, U1.20 (20(SDA))
SDA_5.0V: Q1.3 (D), R2.1, SERIAL.3, SERIAL2.3
SW1_3.3V: U1.35
SW2_3.3V: U1.36
TXD1_3.3V: U1.18 (18(TX1))
TXD2_3.3V: U1.16 (16(TX2))
TXD3_3.3V: U1.14 (14(TX3))
VIN: U1.VIN, X2.2

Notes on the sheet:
SERIAL BUS
(SLIDER/T-BAR IN)
RESET:
CONF:
POWER IN/OUTLET

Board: 2 copper layers, 24 parts (15 on the bottom side), 20 nets, no tracks yet.

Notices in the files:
parts and their libraries:
SparkFun: Licensing: CC v3.0 Share-Alike You are welcome to use this library for commercial purposes.
